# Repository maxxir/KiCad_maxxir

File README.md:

# KiCad_maxxir
My KiCad projects since ~ 05/09/2018 based on KiCad 4.0.7 - 5.0.2 

## Author
* **Ibragimov Maksim aka maxxir**

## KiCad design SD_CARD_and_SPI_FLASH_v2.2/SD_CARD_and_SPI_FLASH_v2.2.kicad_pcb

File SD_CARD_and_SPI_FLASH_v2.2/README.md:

# SD Card and SPI FLASH reader for 5V TTL MCU

### Briefly about the features of the scheme:
* For 5V tolerance used HEF4050BT/CD74HC4050(preferable) Hex Non-Inverting Buffers IC.
* Additional CDI pin. This is the Card Detect pin. It shorts to ground when a card is inserted. 
* SPI FLASH compatible IC: M25P08/25LC256-512-1024/25AA02E48(Microchip OUI MAC GEN)
* Tested and used with [M644_breakout_v1.2d](https://github.com/maxxir/KiCad_maxxir/tree/master/KiCad_M644_breakout_v1.2d)
* Can be connected to any **5V-tolerante Arduino, AVR MEGA, PIC16/18, STM8 etc..**

#### Schematic:

#### This is my own custom board looks like:

## Author
* **Ibragimov Maksim aka maxxir**
22/04/2019

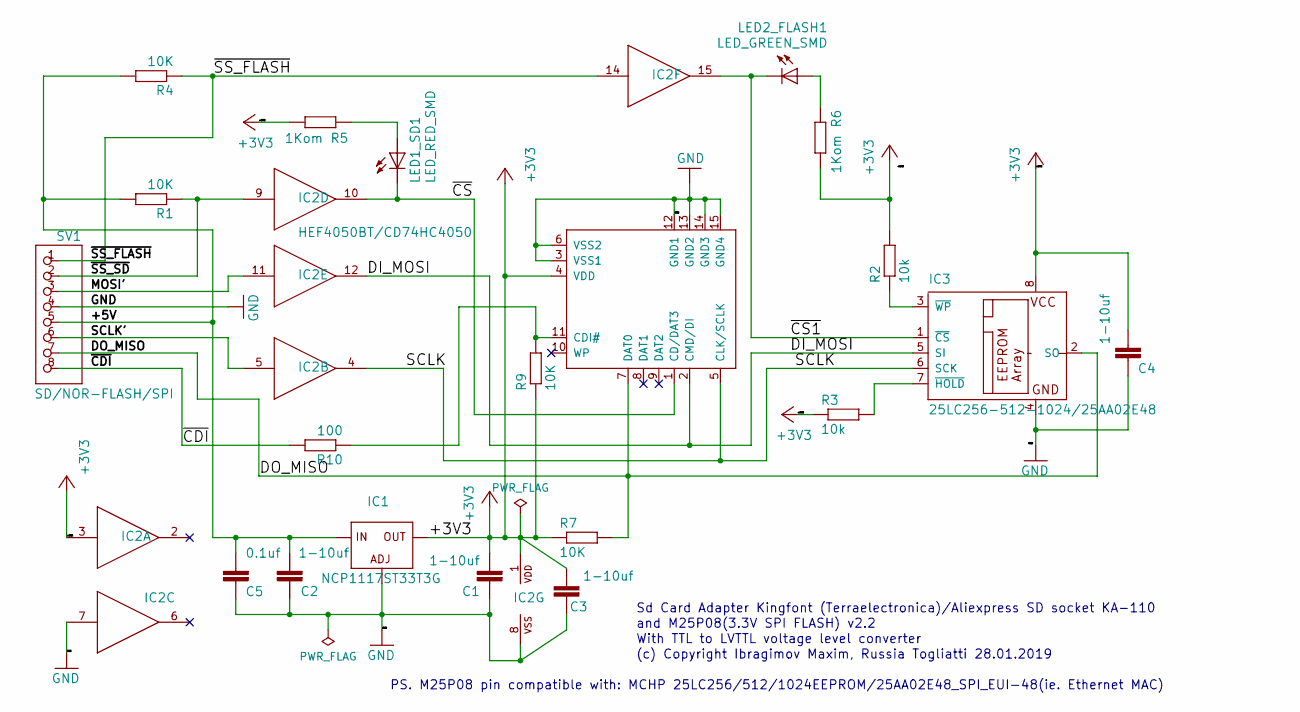
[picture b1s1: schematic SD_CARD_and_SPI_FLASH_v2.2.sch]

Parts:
C1, C2, C3, C4: 1-10uf; C0805H
C5: 0.1uf; C0805H
IC1: NCP1117ST33T3G; SOT223
IC2: HEF4050BT/CD74HC4050; SO16
IC3: 25LC256-512-1024/25AA02E48; SO-08M
LED1_SD1: LED_RED_SMD; CHIPLED_1206
LED2_FLASH1: LED_GREEN_SMD; CHIPLED_1206
R1, R7, R9: 10K; R0805H
R2, R3: 10k; R0805H
R4: 10K; R1206H
R5, R6: 1Kom; R0805H
R10: 100; R0805H
SV1: SD/NOR-FLASH/SPI; 1X08-BIG
U$1: SDCARDVAR2; SDCMF-10915W010

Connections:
+3V3: C1.P$2 (2), C3.P$2 (2), C4.P$2 (2), IC1.4 (OUT), IC2.1 (VDD), IC2.3 (I), IC3.8 (VCC), R2.P$2 (2), R3.P$1 (1), R5.P$2 (2), R6.P$2 (2), R7.P$1 (1), R9.P$1 (1), U$1.4 (VDD)
/+5V: C2.P$2 (2), C5.P$2 (2), IC1.3 (IN), R1.P$2 (2), R4.P$1 (2), SV1.5
/DI_MOSI: IC2.12 (O), IC3.5 (SI), U$1.2 (CMD/DI)
/DO_MISO: IC3.2 (SO), R7.P$2 (2), SV1.7, U$1.7 (DAT0)
/MOSI': IC2.11 (I), SV1.3
/SCLK: IC2.4 (O), IC3.6 (SCK), U$1.5 (CLK/SCLK)
/SCLK': IC2.5 (I), SV1.6
/~CDI: R10.P$2 (2), SV1.8
/~CS: IC2.10 (O), LED1_SD1.C, U$1.1 (CD/DAT3); also elsewhere on the board
/~CS1: IC2.15 (O), IC3.1 (~CS), LED2_FLASH1.C; also elsewhere on the board
/~SS_FLASH: IC2.14 (I), R4.P$2 (1), SV1.1
/~SS_SD: IC2.9 (I), R1.P$1 (1), SV1.2
GND: C1.P$1 (1), C2.P$1 (1), C3.P$1 (1), C4.P$1 (1), C5.P$1 (1), IC1.1 (ADJ), IC2.7 (I), IC2.8 (VSS), IC3.4 (GND), SV1.4, U$1.3 (VSS1), U$1.6 (VSS2), U$1.12 (GND1), U$1.13 (GND2), U$1.14 (GND3), U$1.15 (GND4)
unnamed: IC3.3 (~WP), R2.P$1 (1)
unnamed: IC3.7 (~HOLD), R3.P$2 (2)
unnamed 17: LED1_SD1.A, R5.P$1 (1); also elsewhere on the board
unnamed 18: LED2_FLASH1.A, R6.P$1 (1); also elsewhere on the board
unnamed: R9.P$2 (2), R10.P$1 (1), U$1.11 (CDI#)

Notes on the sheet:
Sd Card Adapter Kingfont (Terraelectronica)/Aliexpress SD socket KA-110
With TTL to LVTTL voltage level converter
(c) Copyright Ibragimov Maxim, Russia Togliatti 28.01.2019
and M25P08(3.3V SPI FLASH) v2.2
PS. M25P08 pin compatible with: MCHP 25LC256/512/1024EEPROM/25AA02E48_SPI_EUI-48(ie. Ethernet MAC)

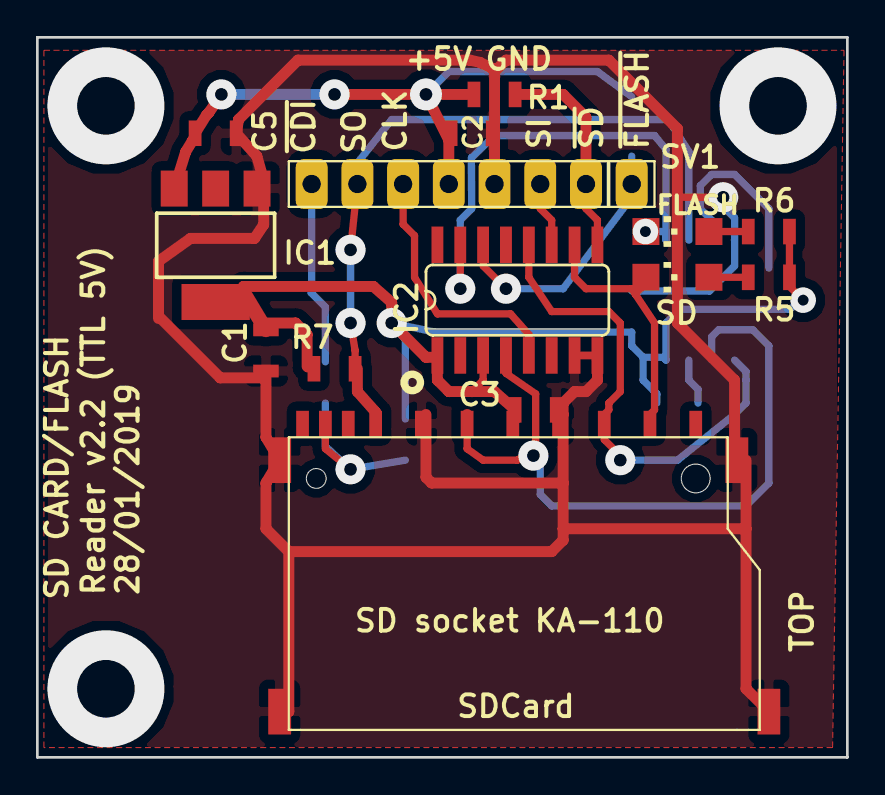
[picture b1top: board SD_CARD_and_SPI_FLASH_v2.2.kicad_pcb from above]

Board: 2 copper layers, 45.0 x 40.0 mm, 21 parts (0 on the bottom side), 18 nets.

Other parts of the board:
FLASH: LED_GREEN_SMD; CHIPLED_1206
SD: LED_RED_SMD; CHIPLED_1206

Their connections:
/~CS: SD.C; also elsewhere on the board
/~CS1: FLASH.C; also elsewhere on the board
unnamed 17: SD.A; also elsewhere on the board
unnamed 18: FLASH.A; also elsewhere on the board

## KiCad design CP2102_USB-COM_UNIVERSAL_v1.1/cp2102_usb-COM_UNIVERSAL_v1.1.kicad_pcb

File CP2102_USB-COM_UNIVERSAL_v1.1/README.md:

# Universal CP2102 USB-COM dongle

With Self/External/Double power mode,

USB lines suppression,

and DTR/RTS for Serial Bootloader (Arduino/AVR, LPCxxxx, STM32)

#### Schematic:

#### This is my own custom board looks like:

## Author
* **Ibragimov Maksim aka maxxir**
20/03/2019

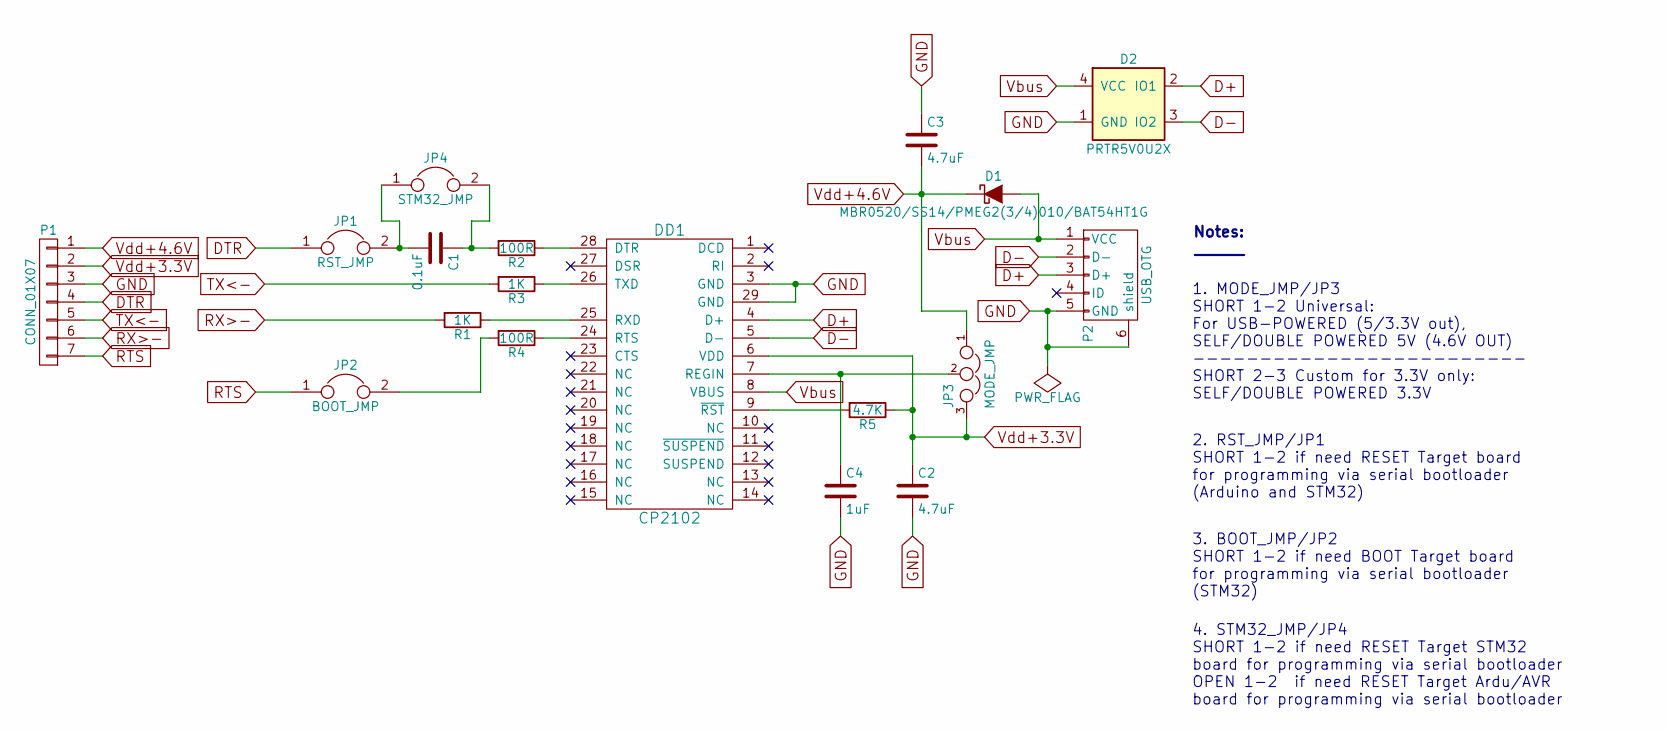
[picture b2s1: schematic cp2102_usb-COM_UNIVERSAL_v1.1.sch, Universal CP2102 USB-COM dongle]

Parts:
C1: 0.1uF; C_0805_HandSoldering
C2, C3: 4.7uF; C_0805_HandSoldering
C4: 1uF; C_0805_HandSoldering
D1: MBR0520/SS14/PMEG2(3/4)010/BAT54HT1G; D_SOD-123
D2: PRTR5V0U2X; SOT-143
DD1: CP2102; QFN-28-1EP_5x5mm_Pitch0.5mm
JP1: RST_JMP; Pin_Header_Straight_1x02_Pitch2.54mm
JP2: BOOT_JMP; Pin_Header_Straight_1x02_Pitch2.54mm
JP3: MODE_JMP; Pin_Header_Straight_1x03_Pitch2.54mm
JP4: STM32_JMP; R_0603_HandSoldering
P1: CONN_01X07; Pin_Header_Straight_1x07_Pitch2.54mm
P2: USB_OTG; USB_Mini-B
R1, R3: 1K; R_0805_HandSoldering
R2, R4: 100R; R_0805_HandSoldering
R5: 4.7K; R_0805_HandSoldering

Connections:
D+: D2.2 (IO1), DD1.4 (D+), P2.3 (D+)
D-: D2.3 (IO2), DD1.5 (D-), P2.2 (D-)
DTR: JP1.1, P1.4
GND: C2.2, C3.1, C4.2, D2.1 (GND), DD1.3 (GND), DD1.29 (GND), P1.3, P2.5 (GND), P2.6 (shield)
unnamed: C1.1, JP4.2, R2.2
unnamed: C1.2, JP1.2, JP4.1
unnamed: C4.1, DD1.7 (REGIN), JP3.2
unnamed: DD1.9 (~RST), R5.2
unnamed: DD1.24 (RTS), R4.1
unnamed: DD1.25 (RXD), R1.1
unnamed: DD1.26 (TXD), R3.1
unnamed: DD1.28 (DTR), R2.1
unnamed: JP2.2, R4.2
RTS: JP2.1, P1.7
RX>-: P1.6, R1.2
TX<-: P1.5, R3.2
Vbus: D1.2 (A), D2.4 (VCC), DD1.8 (VBUS), P2.1 (VCC)
Vdd+3.3V: C2.1, DD1.6 (VDD), JP3.3, P1.2, R5.1
Vdd+4.6V: C3.2, D1.1 (K), JP3.1, P1.1

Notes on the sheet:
1. MODE_JMP/JP3 SHORT 1-2 Universal: For USB-POWERED (5/3.3V out), SELF/DOUBLE POWERED 5V (4.6V OUT) ------------------------- SHORT 2-3 Custom for 3.3V only: SELF/DOUBLE POWERED 3.3V
Notes: ______
2. RST_JMP/JP1 SHORT 1-2 if need RESET Target board for programming via serial bootloader (Arduino and STM32)
3. BOOT_JMP/JP2 SHORT 1-2 if need BOOT Target board for programming via serial bootloader (STM32)
4. STM32_JMP/JP4 SHORT 1-2 if need RESET Target STM32 board for programming via serial bootloader OPEN 1-2 if need RESET Target Ardu/AVR board for programming via serial bootloader

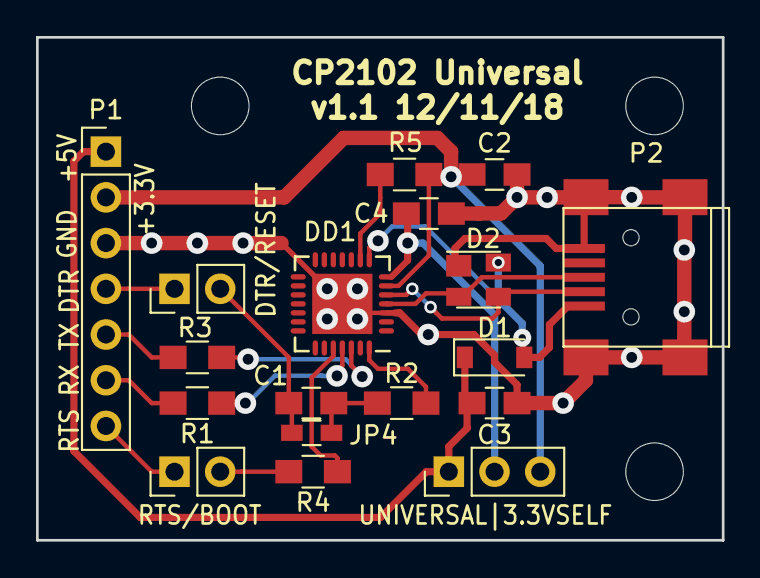
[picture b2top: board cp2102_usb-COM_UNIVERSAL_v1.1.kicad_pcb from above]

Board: 2 copper layers, 38.1 x 27.9 mm, 18 parts (0 on the bottom side), 19 nets.

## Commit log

2019-03-20 Added CP2102_USB-COM_UNIVERSAL_v1.1 project
2019-03-21 Added double power source schematic and pics explain for CP2102 USB-COM
2019-04-08 Added m1284p KiCad generic board
2019-04-09 Changed pics
2019-04-09 Remove 3 diodes
2019-04-13 Slightly corrected schematic layout
2019-04-20 Added *.lib files
2019-04-22 Added SD_CARD_and_SPI_FLASH_v2.2 project
2019-04-22 Added README.md
2019-04-22 Modified 3D top PCB render picture.
2019-04-24 Updated m1284_w5500 photo
